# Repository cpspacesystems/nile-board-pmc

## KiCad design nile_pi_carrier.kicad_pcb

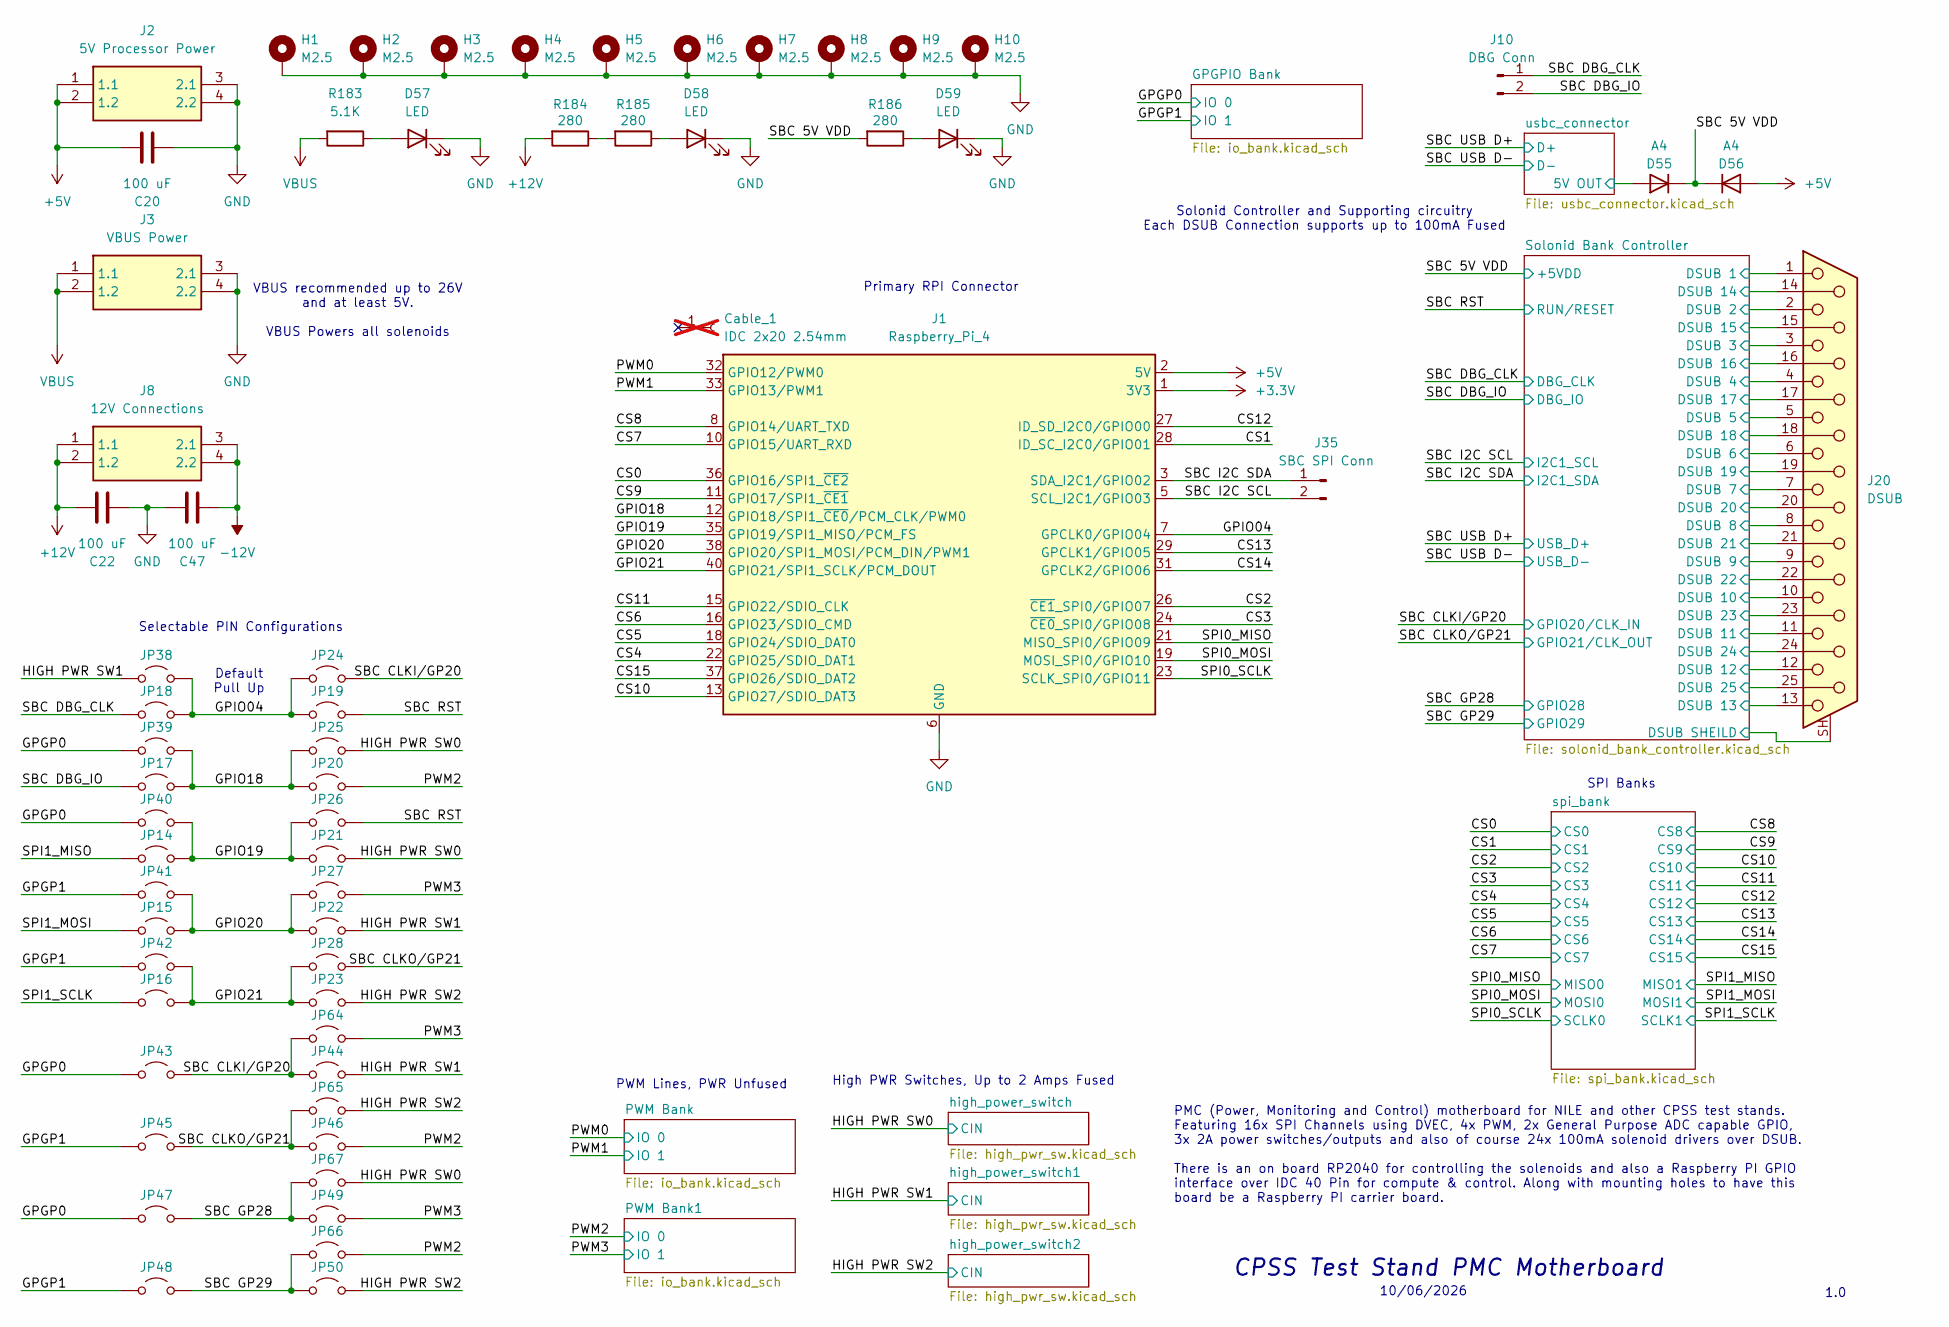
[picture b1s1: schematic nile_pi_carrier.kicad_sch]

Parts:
C20, C22, C47: 100 uF; CP_Radial_D5.0mm_P2.00mm
Cable_1: IDC 2x20 2.54mm; IDC-Header_2x20_P2.54mm_Horizontal; not fitted
D55, D56: A4; D_SOD-123F
D57, D58, D59: LED; D_0603_1608Metric_Pad1.05x0.95mm_HandSolder
H1, H2, H3, H4, H5, H6, H7, H8, H9, H10: M2.5; MountingHole_2.7mm_M2.5_Pad_TopBottom
J1: Raspberry_Pi_4; IDC-Header_2x20_P2.54mm_Horizontal
J2: 5V Processor Power; 26011102; Manufacturer_Part_Number 2601-1102
J3: VBUS Power; 26011102; Manufacturer_Part_Number 2601-1102
J8: 12V Connections; 26011102; Manufacturer_Part_Number 2601-1102
J10: DBG Conn; PinHeader_1x02_P2.54mm_Vertical
J20: DSUB; DSUB-25_Socket_Horizontal_P2.77x2.84mm_EdgePinOffset7.70mm_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
J35: SBC SPI Conn; PinHeader_1x02_P2.54mm_Vertical
JP14, JP15, JP16, JP17, JP18, JP19, JP20, JP21, JP22, JP23, JP24, JP25, JP26, JP27, JP28, JP38, JP39, JP40, JP41, JP42, JP43, JP44, JP45, JP46, JP47, JP48, JP49, JP50, JP64, JP65, JP66, JP67: DBG_CLK; SolderJumper-2_P1.3mm_Open_Pad1.0x1.5mm
R183: 5.1K; R_0805_2012Metric_Pad1.20x1.40mm_HandSolder
R184, R185, R186: 280; R_0402_1005Metric_Pad0.72x0.64mm_HandSolder

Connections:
+3.3V: J1.1 (3V3), J1.17 (3V3); also elsewhere on the board
+5V: C20.1, D56.2 (A), J1.2 (5V), J1.4 (5V), J2.1 (1.1), J2.2 (1.2); also elsewhere on the board
+12V: C22.1, J8.1 (1.1), J8.2 (1.2), R184.2; also elsewhere on the board
-12V: C47.2, J8.3 (2.1), J8.4 (2.2); also elsewhere on the board
/CS0: J1.36 (GPIO16/SPI1_~CE2); also elsewhere on the board
/CS1: J1.28 (ID_SC_I2C0/GPIO01); also elsewhere on the board
/CS2: J1.26 (~CE1_SPI0/GPIO07); also elsewhere on the board
/CS3: J1.24 (~CE0_SPI0/GPIO08); also elsewhere on the board
/CS4: J1.22 (GPIO25/SDIO_DAT1); also elsewhere on the board
/CS5: J1.18 (GPIO24/SDIO_DAT0); also elsewhere on the board
/CS6: J1.16 (GPIO23/SDIO_CMD); also elsewhere on the board
/CS7: J1.10 (GPIO15/UART_RXD); also elsewhere on the board
/CS8: J1.8 (GPIO14/UART_TXD); also elsewhere on the board
/CS9: J1.11 (GPIO17/SPI1_~CE1); also elsewhere on the board
/CS10: J1.13 (GPIO27/SDIO_DAT3); also elsewhere on the board
/CS11: J1.15 (GPIO22/SDIO_CLK); also elsewhere on the board
/CS12: J1.27 (ID_SD_I2C0/GPIO00); also elsewhere on the board
/CS13: J1.29 (GPCLK1/GPIO05); also elsewhere on the board
/CS14: J1.31 (GPCLK2/GPIO06); also elsewhere on the board
/CS15: J1.37 (GPIO26/SDIO_DAT2); also elsewhere on the board
/GPGP0: JP39.1 (A), JP40.1 (A), JP43.1 (A), JP47.1 (A); also elsewhere on the board
/GPGP1: JP41.1 (A), JP42.1 (A), JP45.1 (A), JP48.1 (A); also elsewhere on the board
/GPIO04: J1.7 (GPCLK0/GPIO04), JP18.2 (B), JP19.1 (A), JP24.1 (A), JP38.1 (A)
/GPIO18: J1.12 (GPIO18/SPI1_~CE0/PCM_CLK/PWM0), JP17.2 (B), JP20.1 (A), JP25.1 (A), JP39.2 (B)
/GPIO19: J1.35 (GPIO19/SPI1_MISO/PCM_FS), JP14.2 (B), JP21.1 (A), JP26.1 (A), JP40.2 (B)
/GPIO20: J1.38 (GPIO20/SPI1_MOSI/PCM_DIN/PWM1), JP15.2 (B), JP22.1 (A), JP27.1 (A), JP41.2 (B)
/GPIO21: J1.40 (GPIO21/SPI1_SCLK/PCM_DOUT), JP16.2 (B), JP23.1 (A), JP28.1 (A), JP42.2 (B)
/HIGH PWR SW0: JP21.2 (B), JP25.2 (B), JP67.2 (B); also elsewhere on the board
/HIGH PWR SW1: JP22.2 (B), JP38.2 (B), JP44.2 (B); also elsewhere on the board
/HIGH PWR SW2: JP23.2 (B), JP50.2 (B), JP65.1 (A); also elsewhere on the board
/PWM0: J1.32 (GPIO12/PWM0); also elsewhere on the board
/PWM1: J1.33 (GPIO13/PWM1); also elsewhere on the board
/PWM2: JP20.2 (B), JP46.2 (B), JP66.2 (B); also elsewhere on the board
/PWM3: JP27.2 (B), JP49.2 (B), JP64.2 (B); also elsewhere on the board
/SBC 5V VDD: D55.1 (K), D56.1 (K), R186.2; also elsewhere on the board
/SBC CLKI/GP20: JP24.2 (B), JP43.2 (B), JP44.1 (A), JP64.1 (A); also elsewhere on the board
/SBC CLKO/GP21: JP28.2 (B), JP45.2 (B), JP46.1 (A), JP65.2 (B); also elsewhere on the board
/SBC DBG_CLK: J10.1, JP18.1 (A); also elsewhere on the board
/SBC DBG_IO: J10.2, JP17.1 (A); also elsewhere on the board
/SBC GP28: JP47.2 (B), JP49.1 (A), JP67.1 (A); also elsewhere on the board
/SBC GP29: JP48.2 (B), JP50.1 (A), JP66.1 (A); also elsewhere on the board
/SBC I2C SCL: J1.5 (SCL_I2C1/GPIO03), J35.2; also elsewhere on the board
/SBC I2C SDA: J1.3 (SDA_I2C1/GPIO02), J35.1; also elsewhere on the board
/SBC RST: JP19.2 (B), JP26.2 (B); also elsewhere on the board
/SPI0_MISO: J1.21 (MISO_SPI0/GPIO09); also elsewhere on the board
/SPI0_MOSI: J1.19 (MOSI_SPI0/GPIO10); also elsewhere on the board
/SPI0_SCLK: J1.23 (SCLK_SPI0/GPIO11); also elsewhere on the board
/SPI1_MISO: JP14.1 (A); also elsewhere on the board
/SPI1_MOSI: JP15.1 (A); also elsewhere on the board
/SPI1_SCLK: JP16.1 (A); also elsewhere on the board
/Solonid Bank Controller/DSUB 1: J20.1; also elsewhere on the board
/Solonid Bank Controller/DSUB 2: J20.2; also elsewhere on the board
/Solonid Bank Controller/DSUB 3: J20.3; also elsewhere on the board
/Solonid Bank Controller/DSUB 4: J20.4; also elsewhere on the board
/Solonid Bank Controller/DSUB 5: J20.5; also elsewhere on the board
/Solonid Bank Controller/DSUB 6: J20.6; also elsewhere on the board
/Solonid Bank Controller/DSUB 7: J20.7; also elsewhere on the board
/Solonid Bank Controller/DSUB 8: J20.8; also elsewhere on the board
/Solonid Bank Controller/DSUB 9: J20.9; also elsewhere on the board
/Solonid Bank Controller/DSUB 10: J20.10; also elsewhere on the board
/Solonid Bank Controller/DSUB 11: J20.11; also elsewhere on the board
/Solonid Bank Controller/DSUB 12: J20.12; also elsewhere on the board
/Solonid Bank Controller/DSUB 14: J20.14; also elsewhere on the board
/Solonid Bank Controller/DSUB 15: J20.15; also elsewhere on the board
/Solonid Bank Controller/DSUB 16: J20.16; also elsewhere on the board
/Solonid Bank Controller/DSUB 17: J20.17; also elsewhere on the board
/Solonid Bank Controller/DSUB 18: J20.18; also elsewhere on the board
/Solonid Bank Controller/DSUB 19: J20.19; also elsewhere on the board
/Solonid Bank Controller/DSUB 20: J20.20; also elsewhere on the board
/Solonid Bank Controller/DSUB 21: J20.21; also elsewhere on the board
/Solonid Bank Controller/DSUB 22: J20.22; also elsewhere on the board
/Solonid Bank Controller/DSUB 23: J20.23; also elsewhere on the board
/Solonid Bank Controller/DSUB 24: J20.24; also elsewhere on the board
/Solonid Bank Controller/DSUB 25: J20.25; also elsewhere on the board
/usbc_connector/5V OUT: D55.2 (A); also elsewhere on the board
GND: C20.2, C22.2, C47.1, D57.1 (K), D58.1 (K), D59.1 (K), H1.1 (1_1), H2.1 (1_1), H3.1 (1_1), H4.1 (1_1), H5.1 (1_1), H6.1 (1_1), H7.1 (1_1), H8.1 (1_1), H9.1 (1_1), H10.1 (1_1), J1.6 (GND), J1.9 (GND), J1.14 (GND), J1.20 (GND), J1.25 (GND), J1.30 (GND), J1.34 (GND), J1.39 (GND), J2.3 (2.1), J2.4 (2.2), J3.3 (2.1), J3.4 (2.2), J20.13, J20.SH (PAD); also elsewhere on the board
unnamed: D57.2 (A), R183.1
unnamed: D58.2 (A), R185.1
unnamed: D59.2 (A), R186.1
unnamed: R184.1, R185.2
VBUS: J3.1 (1.1), J3.2 (1.2), R183.2; also elsewhere on the board

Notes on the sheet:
10/06/2026
PWM Lines, PWR Unfused
1.0
Solonid Controller and Supporting circuitry Each DSUB Connection supports up to 100mA Fused
Selectable PIN Configurations
Primary RPI Connector
PMC (Power, Monitoring and Control) motherboard for NILE and other CPSS test stands. Featuring 16x SPI Channels using DVEC, 4x PWM, 2x General Purpose ADC capable GPIO, 3x 2A power switches/outputs and also of course 24x 100mA solenoid drivers over DSUB. There is an on board RP2040 for controlling 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
CPSS Test Stand PMC Motherboard
High PWR Switches, Up to 2 Amps Fused
VBUS recommended up to 26V and at least 5V. VBUS Powers all solenoids
Default Pull Up
SPI Banks

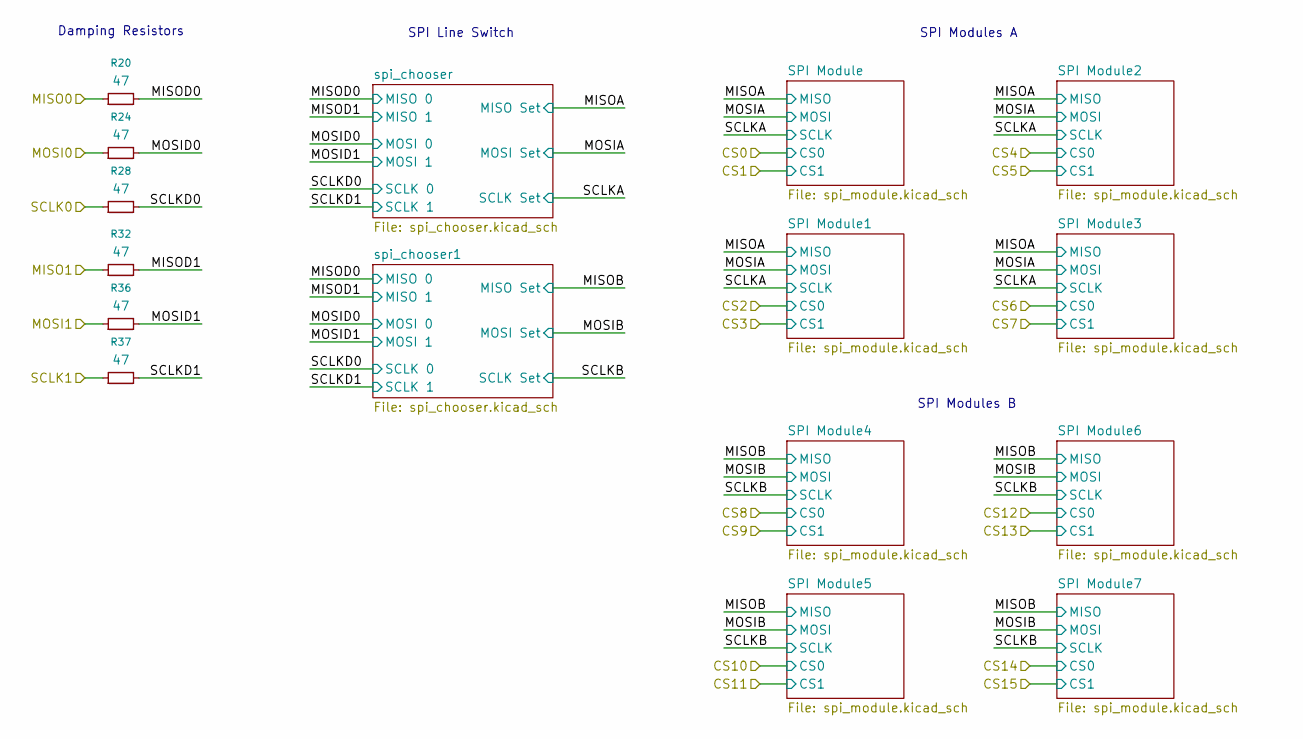
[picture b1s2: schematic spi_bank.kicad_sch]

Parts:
R20, R24, R28, R32, R36, R37: 47; R_0402_1005Metric_Pad0.72x0.64mm_HandSolder

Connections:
/SPI0_MISO: R20.1; also elsewhere on the board
/SPI0_MOSI: R24.1; also elsewhere on the board
/SPI0_SCLK: R28.1; also elsewhere on the board
/SPI1_MISO: R32.1; also elsewhere on the board
/SPI1_MOSI: R36.1; also elsewhere on the board
/SPI1_SCLK: R37.1; also elsewhere on the board
/spi_bank/MISOD0: R20.2; also elsewhere on the board
/spi_bank/MISOD1: R32.2; also elsewhere on the board
/spi_bank/MOSID0: R24.2; also elsewhere on the board
/spi_bank/MOSID1: R36.2; also elsewhere on the board
/spi_bank/SCLKD0: R28.2; also elsewhere on the board
/spi_bank/SCLKD1: R37.2; also elsewhere on the board

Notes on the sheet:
SPI Line Switch
SPI Modules B
Damping Resistors
SPI Modules A

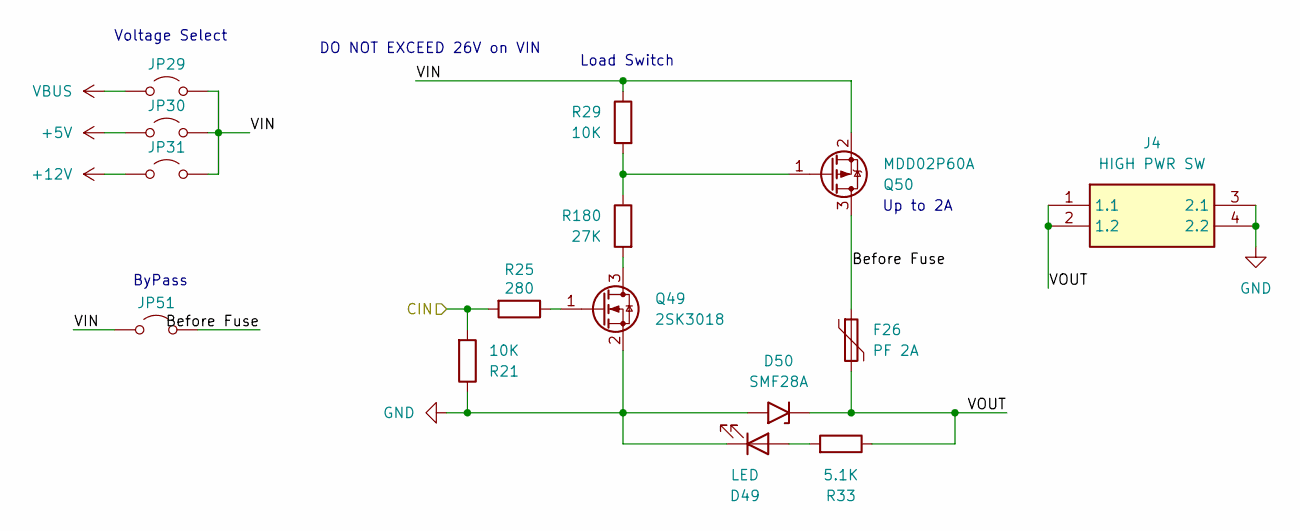
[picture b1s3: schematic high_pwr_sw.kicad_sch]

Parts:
D49: LED; D_0603_1608Metric_Pad1.05x0.95mm_HandSolder
D50: SMF28A; D_SOD-123F
F26: PF 2A; Fuse_2920_7451Metric_Pad2.10x5.45mm_HandSolder
J4: HIGH PWR SW; 26011102; Manufacturer_Part_Number 2601-1102
JP29, JP30, JP31, JP51: DBG_CLK; SolderJumper-2_P1.3mm_Open_Pad1.0x1.5mm
Q49: 2SK3018; SOT-323_SC-70
Q50: MDD02P60A; SOT-23
R21, R29: 10K; R_0402_1005Metric_Pad0.72x0.64mm_HandSolder
R25: 280; R_0402_1005Metric_Pad0.72x0.64mm_HandSolder
R33: 5.1K; R_0805_2012Metric_Pad1.20x1.40mm_HandSolder
R180: 27K; R_0402_1005Metric_Pad0.72x0.64mm_HandSolder

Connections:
+5V: JP30.1 (A); also elsewhere on the board
+12V: JP31.1 (A); also elsewhere on the board
/HIGH PWR SW0: R21.2, R25.2; also elsewhere on the board
/high_power_switch/Before Fuse: F26.1, JP51.2 (B), Q50.3 (D)
/high_power_switch/VIN: JP29.2 (B), JP30.2 (B), JP31.2 (B), JP51.1 (A), Q50.2 (S), R29.1
/high_power_switch/VOUT: D50.1 (A1), F26.2, J4.1 (1.1), J4.2 (1.2), R33.1
GND: D49.1 (K), D50.2 (A2), J4.3 (2.1), J4.4 (2.2), Q49.2 (S), R21.1; also elsewhere on the board
unnamed: D49.2 (A), R33.2
unnamed: Q49.3 (D), R180.2
unnamed: Q49.1 (G), R25.1
unnamed: Q50.1 (G), R29.2, R180.1
VBUS: JP29.1 (A); also elsewhere on the board

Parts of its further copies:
D51, D53: LED; D_0603_1608Metric_Pad1.05x0.95mm_HandSolder
D52, D54: SMF28A; D_SOD-123F
F27, F28: PF 2A; Fuse_2920_7451Metric_Pad2.10x5.45mm_HandSolder
J5, J6: HIGH PWR SW; 26011102; Manufacturer_Part_Number 2601-1102
JP32, JP33, JP34, JP35, JP36, JP37, JP52, JP53: DBG_CLK; SolderJumper-2_P1.3mm_Open_Pad1.0x1.5mm
Q51, Q53: 2SK3018; SOT-323_SC-70
Q52, Q54: MDD02P60A; SOT-23
R41, R49, R61, R69: 10K; R_0402_1005Metric_Pad0.72x0.64mm_HandSolder
R45, R65: 280; R_0402_1005Metric_Pad0.72x0.64mm_HandSolder
R53, R73: 5.1K; R_0805_2012Metric_Pad1.20x1.40mm_HandSolder
R181, R182: 27K; R_0402_1005Metric_Pad0.72x0.64mm_HandSolder

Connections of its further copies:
+5V: JP33.1 (A), JP36.1 (A); also elsewhere on the board
+12V: JP34.1 (A), JP37.1 (A); also elsewhere on the board
/HIGH PWR SW1: R41.2, R45.2; also elsewhere on the board
/HIGH PWR SW2: R61.2, R65.2; also elsewhere on the board
/high_power_switch1/Before Fuse: F27.1, JP52.2 (B), Q52.3 (D)
/high_power_switch1/VIN: JP32.2 (B), JP33.2 (B), JP34.2 (B), JP52.1 (A), Q52.2 (S), R49.1
/high_power_switch1/VOUT: D52.1 (A1), F27.2, J5.1 (1.1), J5.2 (1.2), R53.1
/high_power_switch2/Before Fuse: F28.1, JP53.2 (B), Q54.3 (D)
/high_power_switch2/VIN: JP35.2 (B), JP36.2 (B), JP37.2 (B), JP53.1 (A), Q54.2 (S), R69.1
/high_power_switch2/VOUT: D54.1 (A1), F28.2, J6.1 (1.1), J6.2 (1.2), R73.1
GND: D51.1 (K), D52.2 (A2), D53.1 (K), D54.2 (A2), J5.3 (2.1), J5.4 (2.2), J6.3 (2.1), J6.4 (2.2), Q51.2 (S), Q53.2 (S), R41.1, R61.1; also elsewhere on the board
unnamed: D51.2 (A), R53.2
unnamed: D53.2 (A), R73.2
unnamed: Q51.3 (D), R181.2
unnamed: Q51.1 (G), R45.1
unnamed: Q52.1 (G), R49.2, R181.1
unnamed: Q53.3 (D), R182.2
unnamed: Q53.1 (G), R65.1
unnamed: Q54.1 (G), R69.2, R182.1
VBUS: JP32.1 (A), JP35.1 (A); also elsewhere on the board

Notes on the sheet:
Voltage Select
ByPass
Up to 2A
Load Switch
DO NOT EXCEED 26V on VIN

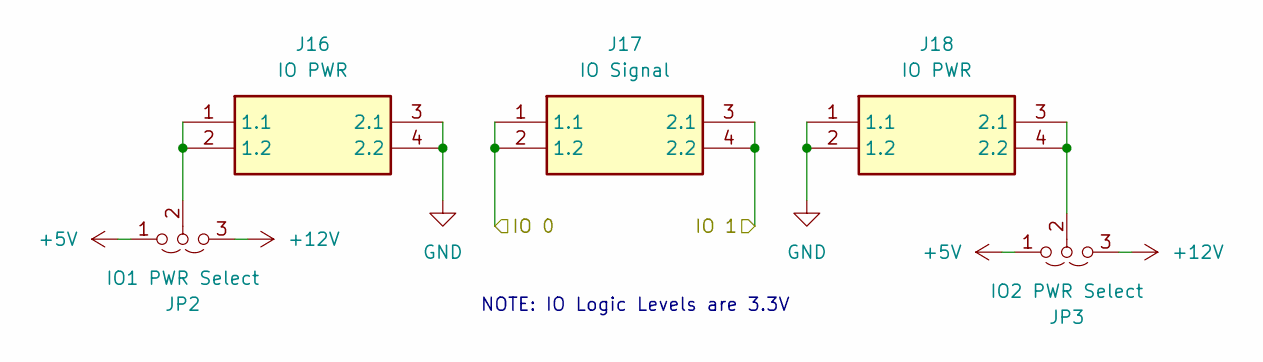
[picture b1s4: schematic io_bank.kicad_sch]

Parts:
J16, J18: IO PWR; 26011102; Manufacturer_Part_Number 2601-1102
J17: IO Signal; 26011102; Manufacturer_Part_Number 2601-1102
JP2: IO1 PWR Select; SolderJumper-3_P1.3mm_Open_Pad1.0x1.5mm_NumberLabels
JP3: IO2 PWR Select; SolderJumper-3_P1.3mm_Open_Pad1.0x1.5mm_NumberLabels

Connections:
+5V: JP2.1 (A), JP3.1 (A); also elsewhere on the board
+12V: JP2.3 (B), JP3.3 (B); also elsewhere on the board
/PWM0: J17.1 (1.1), J17.2 (1.2); also elsewhere on the board
/PWM1: J17.3 (2.1), J17.4 (2.2); also elsewhere on the board
GND: J16.3 (2.1), J16.4 (2.2), J18.1 (1.1), J18.2 (1.2); also elsewhere on the board
unnamed: J16.1 (1.1), J16.2 (1.2), JP2.2 (C)
unnamed: J18.3 (2.1), J18.4 (2.2), JP3.2 (C)

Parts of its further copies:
J19, J32, J34, J38: IO PWR; 26011102; Manufacturer_Part_Number 2601-1102
J33, J37: IO Signal; 26011102; Manufacturer_Part_Number 2601-1102
JP4, JP62: IO1 PWR Select; SolderJumper-3_P1.3mm_Open_Pad1.0x1.5mm_NumberLabels
JP5, JP63: IO2 PWR Select; SolderJumper-3_P1.3mm_Open_Pad1.0x1.5mm_NumberLabels

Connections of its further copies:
+5V: JP4.1 (A), JP5.1 (A), JP62.1 (A), JP63.1 (A); also elsewhere on the board
+12V: JP4.3 (B), JP5.3 (B), JP62.3 (B), JP63.3 (B); also elsewhere on the board
/GPGP0: J33.1 (1.1), J33.2 (1.2); also elsewhere on the board
/GPGP1: J33.3 (2.1), J33.4 (2.2); also elsewhere on the board
/PWM2: J37.1 (1.1), J37.2 (1.2); also elsewhere on the board
/PWM3: J37.3 (2.1), J37.4 (2.2); also elsewhere on the board
GND: J19.3 (2.1), J19.4 (2.2), J32.3 (2.1), J32.4 (2.2), J34.1 (1.1), J34.2 (1.2), J38.1 (1.1), J38.2 (1.2); also elsewhere on the board
unnamed: J19.1 (1.1), J19.2 (1.2), JP4.2 (C)
unnamed: J32.1 (1.1), J32.2 (1.2), JP62.2 (C)
unnamed: J34.3 (2.1), J34.4 (2.2), JP63.2 (C)
unnamed: J38.3 (2.1), J38.4 (2.2), JP5.2 (C)

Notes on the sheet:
NOTE: IO Logic Levels are 3.3V

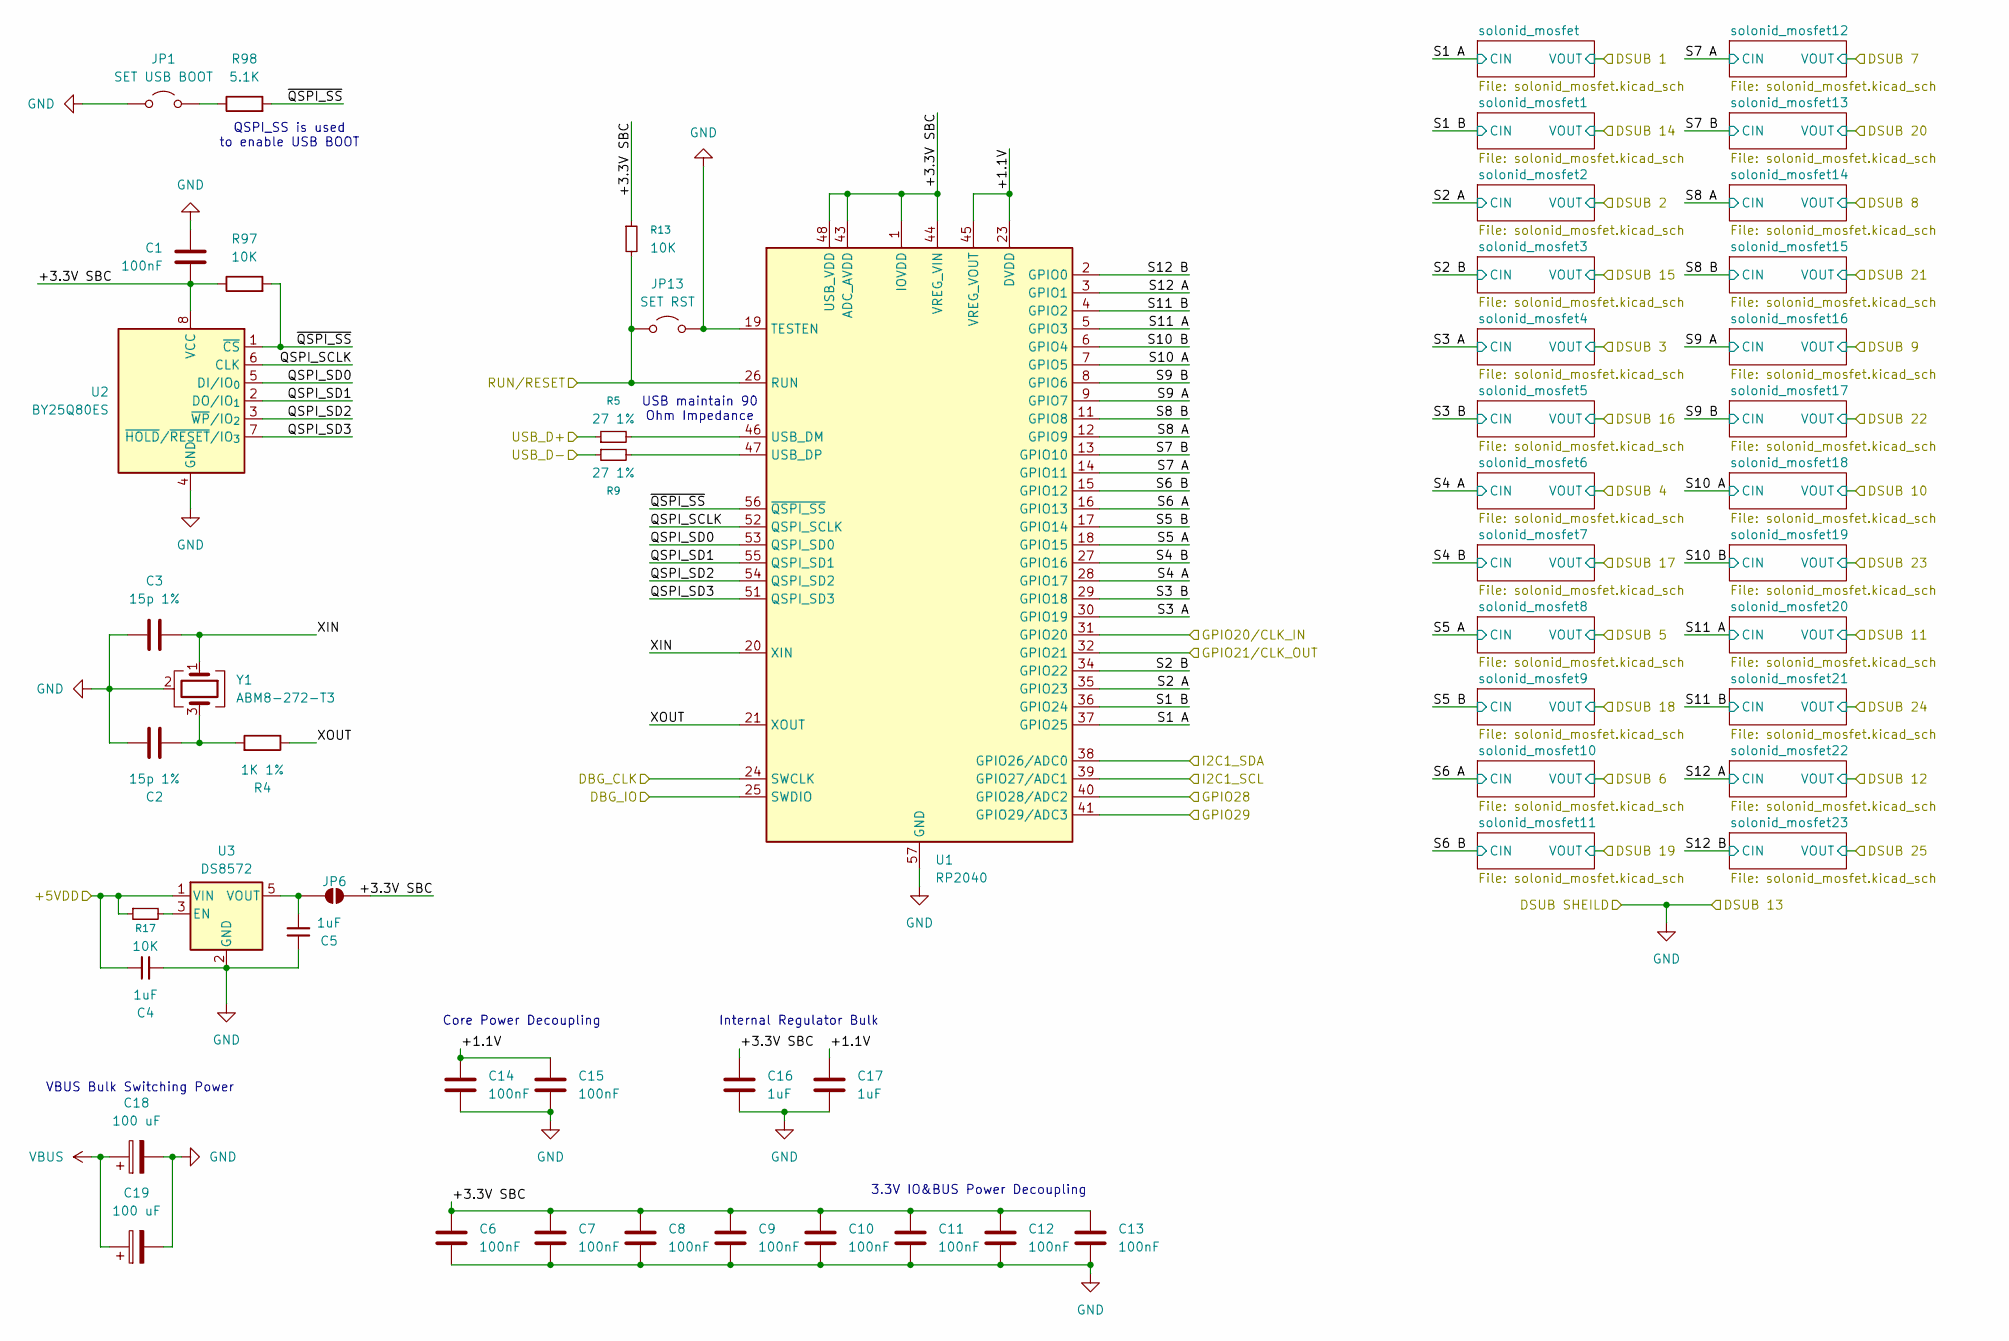
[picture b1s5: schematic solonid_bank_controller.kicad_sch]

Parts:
C1, C6, C7, C8, C9, C10, C11, C12, C13, C14, C15: 100nF; C_0402_1005Metric
C2, C3: 15p 1%; C_0402_1005Metric
C4, C5, C16, C17: 1uF; C_0402_1005Metric
C18, C19: 100 uF; CP_Radial_D5.0mm_P2.00mm
JP1: SET USB BOOT; PinHeader_1x02_P2.54mm_Vertical
JP6: RP2040 3.3V Check; C_0402_1005Metric
JP13: SET RST; PinHeader_1x02_P2.54mm_Vertical
R4: 1K 1%; R_0603_1608Metric
R5, R9: 27 1%; R_0402_1005Metric_Pad0.72x0.64mm_HandSolder
R13, R17, R97: 10K; R_0402_1005Metric_Pad0.72x0.64mm_HandSolder
R98: 5.1K; R_0805_2012Metric_Pad1.20x1.40mm_HandSolder
U1: RP2040; QFN-56-1EP_7x7mm_P0.4mm_EP3.2x3.2mm
U2: BY25Q80ES; TSSOP-8_4.4x3mm_P0.65mm
U3: DS8572; SOT-23-5_HandSoldering
Y1: ABM8-272-T3; Crystal_SMD_Abracon_ABM8AIG-4Pin_3.2x2.5mm

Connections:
/SBC 5V VDD: C4.2, R17.1, U3.1 (VIN); also elsewhere on the board
/SBC CLKI/GP20: U1.31 (GPIO20); also elsewhere on the board
/SBC CLKO/GP21: U1.32 (GPIO21); also elsewhere on the board
/SBC DBG_CLK: U1.24 (SWCLK); also elsewhere on the board
/SBC DBG_IO: U1.25 (SWDIO); also elsewhere on the board
/SBC GP28: U1.40 (GPIO28/ADC2); also elsewhere on the board
/SBC GP29: U1.41 (GPIO29/ADC3); also elsewhere on the board
/SBC I2C SCL: U1.39 (GPIO27/ADC1); also elsewhere on the board
/SBC I2C SDA: U1.38 (GPIO26/ADC0); also elsewhere on the board
/SBC RST: JP13.1 (A), R13.2, U1.26 (RUN); also elsewhere on the board
/SBC USB D+: R5.1; also elsewhere on the board
/SBC USB D-: R9.1; also elsewhere on the board
/Solonid Bank Controller/+1.1V: C14.1, C15.1, C17.1, U1.23 (DVDD), U1.45 (VREG_VOUT), U1.50 (DVDD)
/Solonid Bank Controller/+3.3V SBC: C1.2, C6.1, C7.1, C8.1, C9.1, C10.1, C11.1, C12.1, C13.1, C16.1, JP6.2 (B), R13.1, R97.1, U1.1 (IOVDD), U1.10 (IOVDD), U1.22 (IOVDD), U1.33 (IOVDD), U1.42 (IOVDD), U1.43 (ADC_AVDD), U1.44 (VREG_VIN), U1.48 (USB_VDD), U1.49 (IOVDD), U2.8 (VCC)
/Solonid Bank Controller/QSPI_SCLK: U1.52 (QSPI_SCLK), U2.6 (CLK)
/Solonid Bank Controller/QSPI_SD0: U1.53 (QSPI_SD0), U2.5 (DI/IO_{0})
/Solonid Bank Controller/QSPI_SD1: U1.55 (QSPI_SD1), U2.2 (DO/IO_{1})
/Solonid Bank Controller/QSPI_SD2: U1.54 (QSPI_SD2), U2.3 (~WP/IO_{2})
/Solonid Bank Controller/QSPI_SD3: U1.51 (QSPI_SD3), U2.7 (~HOLD/~RESET/IO_{3})
/Solonid Bank Controller/S1 A: U1.37 (GPIO25); also elsewhere on the board
/Solonid Bank Controller/S1 B: U1.36 (GPIO24); also elsewhere on the board
/Solonid Bank Controller/S2 A: U1.35 (GPIO23); also elsewhere on the board
/Solonid Bank Controller/S2 B: U1.34 (GPIO22); also elsewhere on the board
/Solonid Bank Controller/S3 A: U1.30 (GPIO19); also elsewhere on the board
/Solonid Bank Controller/S3 B: U1.29 (GPIO18); also elsewhere on the board
/Solonid Bank Controller/S4 A: U1.28 (GPIO17); also elsewhere on the board
/Solonid Bank Controller/S4 B: U1.27 (GPIO16); also elsewhere on the board
/Solonid Bank Controller/S5 A: U1.18 (GPIO15); also elsewhere on the board
/Solonid Bank Controller/S5 B: U1.17 (GPIO14); also elsewhere on the board
/Solonid Bank Controller/S6 A: U1.16 (GPIO13); also elsewhere on the board
/Solonid Bank Controller/S6 B: U1.15 (GPIO12); also elsewhere on the board
/Solonid Bank Controller/S7 A: U1.14 (GPIO11); also elsewhere on the board
/Solonid Bank Controller/S7 B: U1.13 (GPIO10); also elsewhere on the board
/Solonid Bank Controller/S8 A: U1.12 (GPIO9); also elsewhere on the board
/Solonid Bank Controller/S8 B: U1.11 (GPIO8); also elsewhere on the board
/Solonid Bank Controller/S9 A: U1.9 (GPIO7); also elsewhere on the board
/Solonid Bank Controller/S9 B: U1.8 (GPIO6); also elsewhere on the board
/Solonid Bank Controller/S10 A: U1.7 (GPIO5); also elsewhere on the board
/Solonid Bank Controller/S10 B: U1.6 (GPIO4); also elsewhere on the board
/Solonid Bank Controller/S11 A: U1.5 (GPIO3); also elsewhere on the board
/Solonid Bank Controller/S11 B: U1.4 (GPIO2); also elsewhere on the board
/Solonid Bank Controller/S12 A: U1.3 (GPIO1); also elsewhere on the board
/Solonid Bank Controller/S12 B: U1.2 (GPIO0); also elsewhere on the board
/Solonid Bank Controller/XIN: C3.1, U1.20 (XIN), Y1.1
/Solonid Bank Controller/XOUT: R4.1, U1.21 (XOUT)
/Solonid Bank Controller/~QSPI_SS: R97.2, R98.2, U1.56 (~QSPI_SS), U2.1 (~CS)
GND: C1.1, C2.2, C3.2, C4.1, C5.2, C6.2, C7.2, C8.2, C9.2, C10.2, C11.2, C12.2, C13.2, C14.2, C15.2, C16.2, C17.2, C18.2, C19.2, JP1.1 (A), JP13.2 (B), U1.19 (TESTEN), U1.57 (GND), U2.4 (GND), U3.2 (GND), Y1.2 (G), Y1.4 (G); also elsewhere on the board
unnamed: C2.1, R4.2, Y1.3
unnamed: JP1.2 (B), R98.1
unnamed: C5.1, JP6.1 (A), U3.5 (VOUT)
unnamed: R5.2, U1.46 (USB_DM)
unnamed: R9.2, U1.47 (USB_DP)
unnamed: R17.2, U3.3 (EN)
VBUS: C18.1, C19.1; also elsewhere on the board

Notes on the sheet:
QSPI_SS is used to enable USB BOOT
USB maintain 90 Ohm Impedance
3.3V IO&BUS Power Decoupling
Core Power Decoupling
Internal Regulator Bulk
VBUS Bulk Switching Power

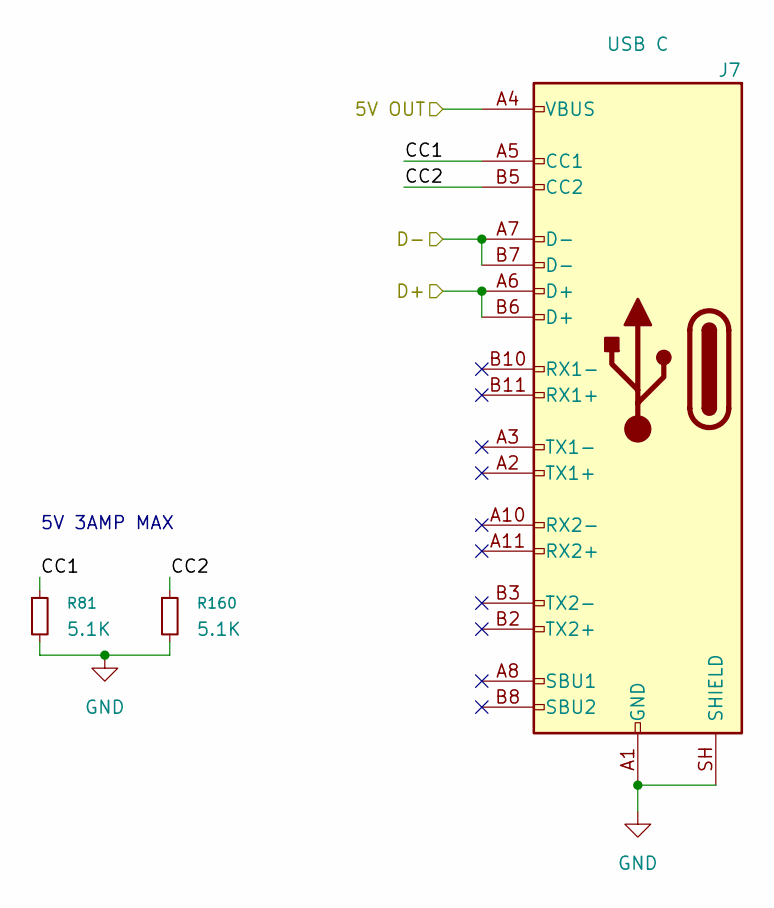
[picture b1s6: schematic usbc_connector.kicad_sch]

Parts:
J7: USB C; USB_C_Receptacle_TC175-24SLB02R-C3
R81, R160: 5.1K; R_0805_2012Metric_Pad1.20x1.40mm_HandSolder

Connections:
/SBC USB D+: J7.A6 (D+), J7.B6 (D+); also elsewhere on the board
/SBC USB D-: J7.A7 (D-), J7.B7 (D-); also elsewhere on the board
/usbc_connector/5V OUT: J7.A4 (VBUS), J7.A9 (VBUS), J7.B4 (VBUS), J7.B9 (VBUS); also elsewhere on the board
/usbc_connector/CC1: J7.A5 (CC1), R81.1
/usbc_connector/CC2: J7.B5 (CC2), R160.1
GND: J7.A1 (GND), J7.A12 (GND), J7.B1 (GND), J7.B12 (GND), J7.SH (SHIELD), R81.2, R160.2; also elsewhere on the board

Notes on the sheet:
5V 3AMP MAX

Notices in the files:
nile_pi_carrier.kicad_pcb:
© Alvin He
